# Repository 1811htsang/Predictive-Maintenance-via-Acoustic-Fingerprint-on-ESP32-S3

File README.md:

# Predictive-Maintenance-via-Acoustic-Fingerprint-on-ESP32-S3

## Introduction

This project focuses on developing a high-speed data sampling system for predictive maintenance of hard-to-detect failures in industrial equipment, specifically targeting bearing failures at a sampling rate of 96kHz. The system utilizes the ESP32-S3 as a cost-effective central processor, combined with sensors such as the PCM1808 and TCT40-16R to capture full multi-band audio data. The entire project is designed end-to-end, from the physical PCB circuit to the accompanying software.

---

## Structure

- `docs/`: Documentation and design notes.
  - `notes/`: Development notes and considerations.
    - `analysis/`: Analysis of requirements and design decisions.
    - `peripherals/`: Details on peripheral usage and configuration.
    - `components/`: Information on hardware components used in the project.
  - `references/`: Reference materials and datasheets.
- `project-architecture/`: Overview of the project architecture, containing main driver code structure.
- `project-kicadspace/`: KiCad design files for the PCB layout and schematic.
- `project-obsidianspace/`: Obsidian vault for project notes and documentation.

---

## Features

- **Microcontroller**: ESP32-S3-DevKitC N16R8 for high-performance processing and connectivity.
- **Peripherals**:
  - SPI for communication with external microSD card for data storage
  - I2S for audio data acquisition from the PCM1808.
  - GPIO for status indicators and control signals.
  - RCC for reset & clock management.
  - I2C for LCD interfacing (optional).
  - DMA for efficient data transfer from ADC to memory.

---

## Hardware Components

Note that this sections can be expand with new requirements in the future.

- ESP32-S3-DevKitC N16R8 microcontroller
- MAX9812 microphone amplifier
- PCM1808 ADC
- TL072IDT operational amplifier
- TCT40-16R MEMS microphone
- JP-313B for 3.5mm Jack audio input
- MicroSD card module for data storage
- Optional: I2C LCD display for status monitoring

---

## References

- Do You Hear What I Hear?: Fingerprinting Smart Devices Through Embedded Acoustic Components by Anupam Das, Nikita Borisov, Matthew Caesar, 2014.
- Audio Data Acquisition System Design Based on ARM and DSP by Yongxin Wang, 2015.
- Predictive Maintenance with Sensor Data Analytics on a Raspberry Pi-Based Experimental Platform by Shang-Yi Chuang, Nilima Sahoo, Hung-Wei Lin and Yeong-Hwa Chang, 2019.
- Challenges in predictive maintenance – A review by P.Nunes, J.Santos, E.Rocha, 2022.
- Predictive Maintenance: An Embedded System Approach by Igor Tedeschi Franco, Rodrigo Marques de Figueiredo, 2022.
- Device Fingerprinting for Cyber-Physical Systems: A Survey by Vịay Kumar and Kolin Paul, 2023.
- Anomaly Detection In IoT Sensor Data Using Machine Learning Techniques For Predictive Maintenance In Smart Grids by Edwin Omol, Lucy Mburu, Paul Abuonji,  Dorcas Onyango, 2024.
- Application of Embedded Systems in Industrial IoT for Predictive Maintenance by Elena García-Ortega, 2024.
- Explainable Predictive Maintenance: A Survey of Current Methods, Challenges and Opportunities by Logan Cummins, Alex Sommers, Somayeh Bakhtiari Ramezani, Supid Mittal, Joseph Jabour, Maria Seale and Shahram Rahimi, 2024.
- Acoustic fingerprint in vehicle manufacturing as a basis for future applications by Jozsef Nagy, Istvan Lakatos, 2025.
- End-to-End Methodology for Predictive Maintenance Based on Fingerprint Routines and Anomaly Detection for Machine Tool Rotary Components by Amaia Arregi, Aitor Barrutia and Iñigo Bediaga, 2025.

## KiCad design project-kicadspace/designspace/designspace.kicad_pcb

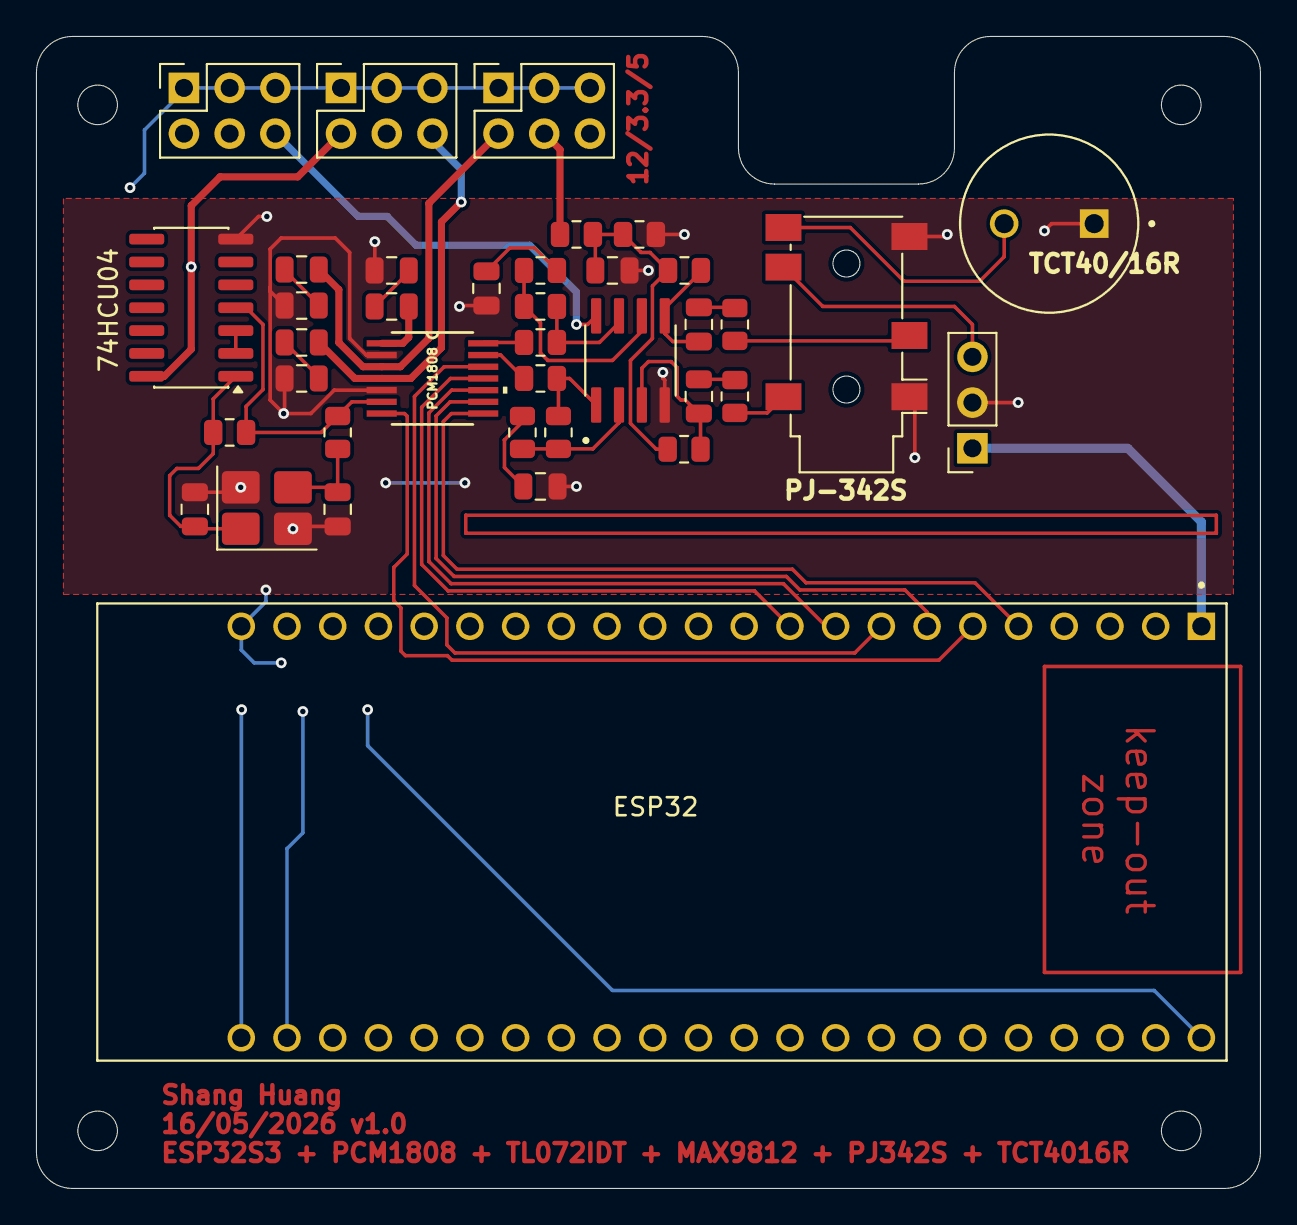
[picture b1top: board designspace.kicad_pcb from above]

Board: 2 copper layers, 68.0 x 64.0 mm, 34 parts (0 on the bottom side), 33 nets.

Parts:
C3, C15: 1uF; C_0805_2012Metric
C4, C6, C8, C10, C13, C14: 10uF; C_0805_2012Metric
C5, C7, C9: 0.1uF; C_0805_2012Metric
C11, C12: 27pF; C_0805_2012Metric
ESP32: ESP32-S3-DEVKITC-1-N8R8
INVBUF1: 74HCU04; SO-14_3.9x8.65mm_P1.27mm
J1: PJ-313B; pj342s audio jack
MK2: TCT40-16R
Op-amp2: TL072; TL072IDT
Osc1: 24.576MHz; Crystal_SMD_3225-4Pin_3.2x2.5mm_HandSoldering
PCM1808: PCM1808PWR; PW14
R2, R3, R4, R10, R11: 10kOhm; R_0805_2012Metric
R5, R6, R9, R15: 1kOhm; R_0805_2012Metric
R7, R13: 100kOhm; R_0805_2012Metric
R8, R12: 1MOhm; R_0805_2012Metric
R14: 2.2kOhm; R_0805_2012Metric

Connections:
3.3V: C8.1, ESP32.3V3, INVBUF1.14 (VCC), PCM1808.4 (VDD)
5V: C4.1, PCM1808.3 (VCC), R2.1
GND: C5.1, C6.2, C9.1, C10.1, C11.2, C12.2, C13.1, C14.1, ESP32.GND, ESP32.GND1, ESP32.GND2, ESP32.GND3, INVBUF1.7 (GND), J1.G, J1.S, MK2.1 (-), Op-amp2.4 (V-), Osc1.2 (G), Osc1.4 (G), PCM1808.2 (AGND), PCM1808.5 (DGND), R3.2
unnamed: C3.2, R10.1
unnamed: C4.2, C5.2
unnamed: C6.1, C7.1
unnamed: C8.2, C9.2
unnamed: C10.2, R5.1
unnamed: C11.1, INVBUF1.1, Osc1.1, R8.1
unnamed: C12.1, Osc1.3, R9.1
unnamed: C13.2, R2.2, R3.1, R7.1, R12.2
unnamed: C14.2, R14.1
unnamed: C15.2, R11.1
unnamed: INVBUF1.2, INVBUF1.3
unnamed: J1.R1, R11.2
unnamed: J1.T, R10.2
unnamed: J1.R2, MK2.2 (+)
unnamed: Op-amp2.1, R4.1, R6.1
unnamed: Op-amp2.7, R13.1, R15.2
unnamed: C3.1, Op-amp2.3 (+), R7.2
unnamed: Op-amp2.2 (-), R4.2, R5.2
unnamed: C15.1, Op-amp2.5 (+), R12.1
unnamed: Op-amp2.6 (-), R13.2, R14.2
unnamed: ESP32.GPIO5, PCM1808.8 (BCK)
unnamed: ESP32.GPIO7, PCM1808.9 (DOUT)
unnamed: ESP32.GPIO15, PCM1808.12 (FMT)
unnamed: ESP32.GPIO6, PCM1808.7 (LRCK)
unnamed: ESP32.GPIO16, PCM1808.10 (MD0)
unnamed: ESP32.GPIO17, PCM1808.11 (MD1)
unnamed: INVBUF1.4, PCM1808.6 (SCKI), R8.2, R9.2
unnamed: PCM1808.13 (VINL), R6.2
unnamed: PCM1808.14 (VINR), R15.1
unnamed: C7.2, PCM1808.1 (VREF)

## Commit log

2026-05-23 docs(to-do): add task to include LDO for noise reduction and audio quality improvement
2026-05-24 feat(build): include app_main.c in component registration
2026-05-24 docs(to-do): update tasks for LDO consideration and data processing server configuration
2026-05-28 feat(pcb): update curve position align center with audio jack
2026-05-28 docs(to-do): update LDO consideration and add new tasks for PCB design and audio processing
2026-05-28 feat(lib): restructure library components and add MFCC implementation
2026-06-06 feat(esp-dsp, mfcc): import esp-dsp into project and some implement for mfcc
